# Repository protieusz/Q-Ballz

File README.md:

# Q-Ballz
Q-Ballz, inspired by an anime with 2 trackballs, 2x CORE-A Mcus, 34 keys, 10 RGBs

# Description
Case design shape was inspired by a Neo Zeon prototype mobile suit, [Qubeley](https://gundam.fandom.com/wiki/AMX-004_Qubeley), one of the underrated MS from the Gundam Zeta series hence the name "Q-Ballz". Q-Ballz uses 2 trackballs as the previous OverLord, where this time the top ball is mouse movement and bottom is scrolling. The size of the custom keeb design is similar size to
Sachiel or the Excelsior.  Nice and compact for office use and wow factor with 10 RGBs on the vents and eyes. There might be some flaws on the "notches" that clips both top and bottom case together. Slight oversight but can make it work
with tiny DIY. Print at your own risk.

**Oct 19, 2024:** Q-Ballz is fully build and functional. All RGBs on both sides are fully working. Thanks to **Drashna Jael're** from fingerpunch discord for helping me out with QMK part and validation of my solder hack. Please see below pic for the hack details.

**Oct 17, 2024:** Q-Ballz fully build but only RIGHT side RGBs are fully working. Voltage and continuity all checks out. So I suspect it might be the QMK code.  Hopefully the QMK code can be fixed.
As for the effect of having set color RGBs for each sides, I tried using transparent colored plastic but it turns out that they are too thin and the RGB lights overpowered it. If someone can program where the RGBs on the right are always constant Blue for the circle vents while the Right eye is Pink, right vents pink while the rest of the LEFT side is pink. Anywayz Qubeley custom keeb mission accomplished.

**Sept 18, 2024:** PCB print will not be printed until October ish since my PMW3360 sensors and SA keycaps have not arrive yet. I am very excited for this build design.

# Disclaimer
This work is a non-commercial fan creation of custom keyboard case and PCB in the shape of Qubeley from the Gundam Zeta series. It is made out of love and respect for the Gundam Zeta series. All rights to Gundam and related content are owned by Bandai Namco Holdings Inc and its associated companies. The images, names, storylines and other elements of Gundam used in this work are the property of their respective copyright holders. Unauthorized commercial use is strictly prohibited. The license of this design reflects not for commercial use. Only the PCB files, QMK source will be open source. The case files due to copyright issues will not be open sourced.

Please print and use the case and PCB at your own risk. QMK code is derived from the QMK documentation and copy over from my OverLord build.

# Full Build
Oct 17, 2024

I had to think outside the box by making the RGBs working on both sides. I edit the config.h RGB split settings to (0, 10) to have all the RGBs sourced from the RIGHT side for all the RGBs.
Then I solder the DOUT from the RIGHT side to the DIN of the LEFT for the RGBs and it worked! Shout out to **Drashna Jael're** from fingerpunch Discord channel for helping me out with QMK part and validation of my solder hack.

# Renders

# License

</a></p>

You are free to:

Share — copy and redistribute the material in any medium or format

Adapt — remix, transform, and build upon the material

The licensor cannot revoke these freedoms as long as you follow the license terms.
Under the following terms:

Attribution — You must give appropriate credit, provide a link to the license, and indicate if changes were made. You may do so in any reasonable manner, but not in any way that suggests the licensor endorses you or your use.

NonCommercial — You may not use the material for commercial purposes.

ShareAlike — If you remix, transform, or build upon the material, you must distribute your contributions under the same license as the original.

No additional restrictions — You may not apply legal terms or technological measures that legally restrict others from doing anything the license permits.

Q-Ballz by ProtieusKeebs is licensed under [CC BY-NC-SA 4.0](https://creativecommons.org/licenses/by-nc-sa/4.0/?ref=chooser-v1)

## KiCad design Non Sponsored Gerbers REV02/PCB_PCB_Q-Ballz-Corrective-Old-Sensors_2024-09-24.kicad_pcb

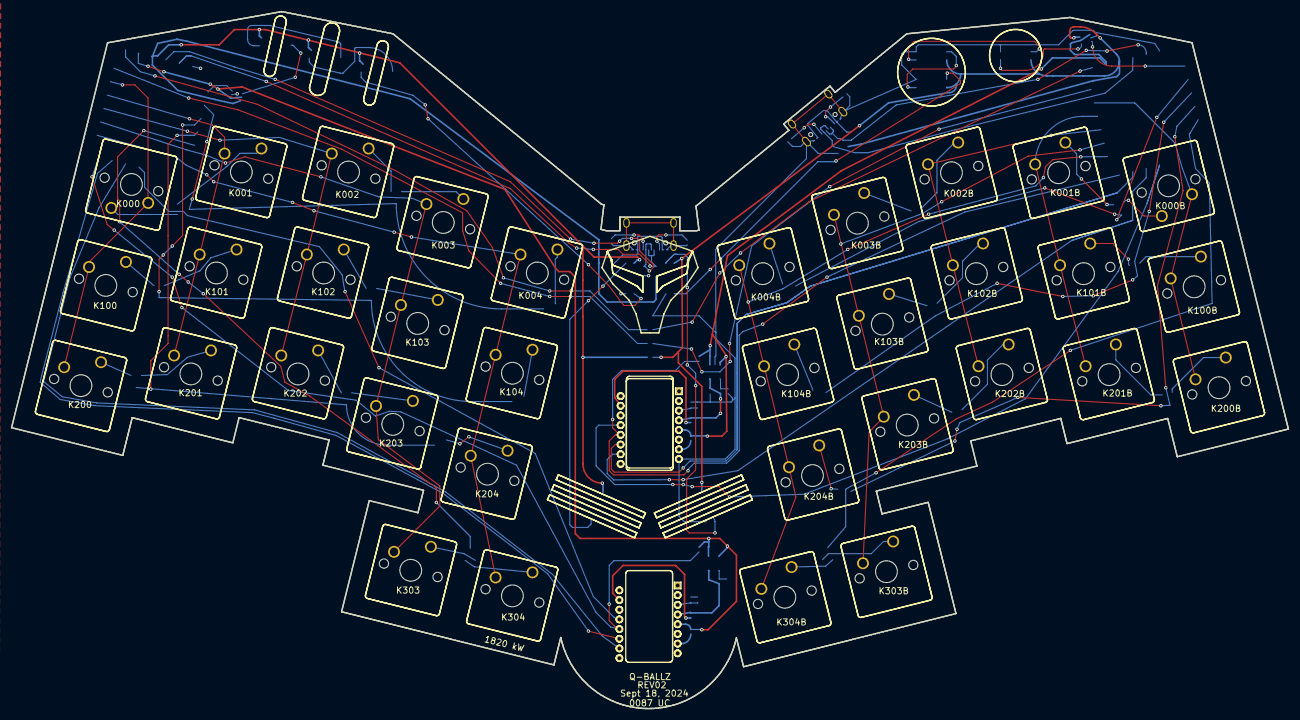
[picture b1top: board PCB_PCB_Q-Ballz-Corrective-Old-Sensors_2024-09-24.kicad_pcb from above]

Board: 2 copper layers, 234.5 x 128.0 mm, 104 parts (0 on the bottom side), 102 nets.

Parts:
C17, C17B, C19, C19B, C20, C20B: 4.7uF; C0402
C18, C18B: 100nF; C0402
D000, D000B, D002, D002B, D004, D004B, D100, D100B, D102, D102B, D104, D104B, D200, D200B, D202, D202B, D204, D204B, D303, D303B: BAV70-C68978; SOT-23-3_L3.0-W1.7-P0.95-LS2.9-BR
D6, D11: PRTR5V0U2X,215; SOT-143_L2.9-W1.3-P1.92-LS2.3-BR
F1, F3: nSMD050; F1206
JP1GND, JP2RX, JP3TX, JP4+5V: SOLDER JUMPER PADS; SOLDER BRIDGE JUMPER PADS
K000, K000B, K001, K001B, K002, K002B, K003, K003B, K004, K004B, K100, K100B, K101, K101B, K102, K102B, K103, K103B, K104, K104B, K200, K200B, K201, K201B, K202, K202B, K203, K203B, K204, K204B, K303, K303B, K304, K304B: 100; CHERRY_MX_100_MILLMAX
R1, R2, R3, R4: 5.1kΩ; R0402
R10, R10B, R12, R12B, R13, R13B: 10kΩ; R0402
R11, R11B: 39Ω; R0402
R14, R14B: 15kΩ; R0402
U01, U01R, U02, U02R, U03, U03R, U04, U04R, U05, U05R: SK6812MINI-E_C5149201; LED-SMD_L3.2-W2.8-TR
U1L, U1R: 5; RP2040-CORE-A
U6L, U6R: SN74LVC1T45DCKR; SC-70-6_L2.2-W1.3-P0.65-LS2.2-BR
U7, U7B: PMW3360DM-T2QU; PMW3360DM-T2QU.PACK
U8, U8B: AP2127K-ADJTRG1; SOT-23-5_L3.0-W1.7-P0.95-LS2.8-BR
USBCL: TYPE-C-31-M-12; USB-C_SMD-TYPE-C-31-M-12
USBCR: TYPE-C-31-M-12; USB-C_SMD-TYPE-C-31-M-12

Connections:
+2V: C20B.2, R11B.2, R14B.2, U7B.4, U8B.5
+2VL: C20.2, R11.2, R14.2, U7.4, U8.5
+3V3: C19B.2, R10B.2, R12B.2, U1R.15, U6R.1, U6R.5, U7B.5, U8B.1, U8B.3
+3V3L: C19.2, R10.2, R12.2, U1L.15, U6L.1, U6L.5, U7.5, U8.1, U8.3
+5V: D6.4, F1.2, JP4+5V.2, U01R.1, U1R.16, U02R.1, U03R.1, U04R.1, U05R.1, U6R.6
+5VL: D11.4, F3.2, JP4+5V.1, U01.1, U1L.16, U02.1, U03.1, U04.1, U05.1, U6L.6
C18_1: C17.1, C18.1, U7.3
COL0L: K000.2, K100.2, K200.2, U1L.12
COL0R: K000B.2, K100B.2, K200B.2, U1R.12
COL1L: K001.2, K101.2, K201.2, U1L.11
COL1R: K001B.2, K101B.2, K201B.2, U1R.11
COL2L: K002.2, K102.2, K202.2, U1L.10
COL2R: K002B.2, K102B.2, K202B.2, U1R.10
COL3L: K003.2, K103.2, K203.2, K303.2, U1L.9
COL3R: K003B.2, K103B.2, K203B.2, K303B.2, U1R.9
COL4L: K004.2, K104.2, K204.2, K304.2, U1L.8
COL4R: K004B.2, K104B.2, K204B.2, K304B.2, U1R.8
CSL: U1L.4, U7.13
CSR: U1R.4, U7B.13
D+L: D11.3, U1L.18, USBCL.A6, USBCL.B6
D+R: D6.3, U1R.18, USBCR.A6, USBCR.B6
D-L: D11.2, U1L.17, USBCL.A7, USBCL.B7
D-R: D6.2, U1R.17, USBCR.A7, USBCR.B7
GND: C17B.2, C18B.2, C19B.1, C20B.1, D6.1, JP1GND.2, R3.1, R4.2, R13B.1, U01R.3, U1R.19, U02R.3, U03R.3, U04R.3, U05R.3, U6R.2, U7B.8, U8B.2, USBCR.0, USBCR.1, USBCR.2, USBCR.3, USBCR.A1, USBCR.A12, USBCR.B1, USBCR.B12
GNDL: C17.2, C18.2, C19.1, C20.1, D11.1, JP1GND.1, R1.2, R2.1, R13.1, U01.3, U1L.19, U02.3, U03.3, U04.3, U05.3, U6L.2, U7.8, U8.2, USBCL.0, USBCL.1, USBCL.2, USBCL.3, USBCL.A1, USBCL.A12, USBCL.B1, USBCL.B12
K000B_1: D000B.2, K000B.1
K000_1: D000.1, K000.1
K001B_1: D000B.1, K001B.1
K001_1: D000.2, K001.1
K002B_1: D002B.2, K002B.1
K002_1: D002.1, K002.1
K003B_1: D002B.1, K003B.1
K003_1: D002.2, K003.1
K004B_1: D004B.2, K004B.1
K004_1: D004.1, K004.1
K100B_1: D100B.2, K100B.1
K100_1: D100.1, K100.1
K101B_1: D100B.1, K101B.1
K101_1: D100.2, K101.1
K102B_1: D102B.2, K102B.1
K102_1: D102.1, K102.1
K103B_1: D102B.1, K103B.1
K103_1: D102.2, K103.1
K104B_1: D104B.2, K104B.1
K104_1: D104.1, K104.1
K200B_1: D200B.2, K200B.1
K200_1: D200.1, K200.1
K201B_1: D200B.1, K201B.1
K201_1: D200.2, K201.1
K202B_1: D202B.2, K202B.1
K202_1: D202.1, K202.1
K203B_1: D202B.1, K203B.1
K203_1: D202.2, K203.1
K204B_1: D204B.2, K204B.1
K204_1: D204.1, K204.1
K303B_1: D303B.2, K303B.1
K303_1: D303.1, K303.1
K304B_1: D303B.1, K304B.1
K304_1: D303.2, K304.1
MISOL: R12.1, U1L.7, U7.12
MISOR: R12B.1, U1R.7, U7B.12
MOSIL: U1L.6, U7.11
MOSIR: U1R.6, U7B.11
R3_2: R3.2, USBCR.B5
R4_1: R4.1, USBCR.A5
R10_1: R10.1, U7.7
R11_1: R11.1, U7.15
R14_1: R13.2, R14.1, U8.4
RGB: U01.4, U6L.4
RGBMCU: U1L.20, U6L.3
RGBMCUR: U1R.20, U6R.3
RGBR: U01R.4, U6R.4
ROW0L: D000.3, D002.3, D004.3, U1L.21
ROW0R: D000B.3, D002B.3, D004B.3, U1R.21
ROW1L: D100.3, D102.3, D104.3, U1L.22
ROW1R: D100B.3, D102B.3, D104B.3, U1R.22
ROW2L: D200.3, D202.3, D204.3, U1L.23
ROW2R: D200B.3, D202B.3, D204B.3, U1R.23
ROW3L: D303.3, U1L.24
ROW3R: D303B.3, U1R.24
RXL: JP2RX.1, U1L.14
RXR: JP2RX.2, U1R.14
SCKL: U1L.5, U7.10
SCKR: U1R.5, U7B.10
TXL: JP3TX.1, U1L.13
TXR: JP3TX.2, U1R.13
U01R_2: U01R.2, U02R.4
U02R_2: U02R.2, U03R.4
U02_4: U01.2, U02.4
U03_2: U03.2, U04.4
U03_4: U02.2, U03.4
U04R_4: U03R.2, U04R.4
U04_2: U04.2, U05.4
U05R_4: U04R.2, U05R.4
U7B_3: C17B.1, C18B.1, U7B.3
U7B_7: R10B.1, U7B.7
U7B_15: R11B.1, U7B.15
U8B_4: R13B.2, R14B.1, U8B.4
USBCL_A5: R1.1, USBCL.A5
USBCL_B5: R2.2, USBCL.B5
VBUSL: F3.1, USBCL.A4, USBCL.A9, USBCL.B4, USBCL.B9
VBUSR: F1.1, USBCR.A4, USBCR.A9, USBCR.B4, USBCR.B9

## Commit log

2024-09-18 Update LICENSE
2024-09-18 Case files
2024-09-18 PCB Sketch
2024-09-26 QMK source
2024-09-26 QMK firmware
2024-10-14 Gerbers, kicad, etc.
2024-10-18 Converted EasyEDA to Kicad files
2024-10-18 Only half of RGBs are working for now.
2024-10-19 Update config.h RGB settings
2024-10-19 Working RGBs with soldering hack

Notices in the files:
README.md:
https://mirrors.creativecommons.org/presskit/icons/cc.svg?ref=chooser-v1https://mirrors.creativecommons.org/presskit/icons/by.svg?ref=chooser-v1https://mirrors.creativecommons.org/presskit/icons/nc.svg?ref=chooser-v1
